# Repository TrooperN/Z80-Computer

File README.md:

# Z80-Computer

## This is a Work in Progress

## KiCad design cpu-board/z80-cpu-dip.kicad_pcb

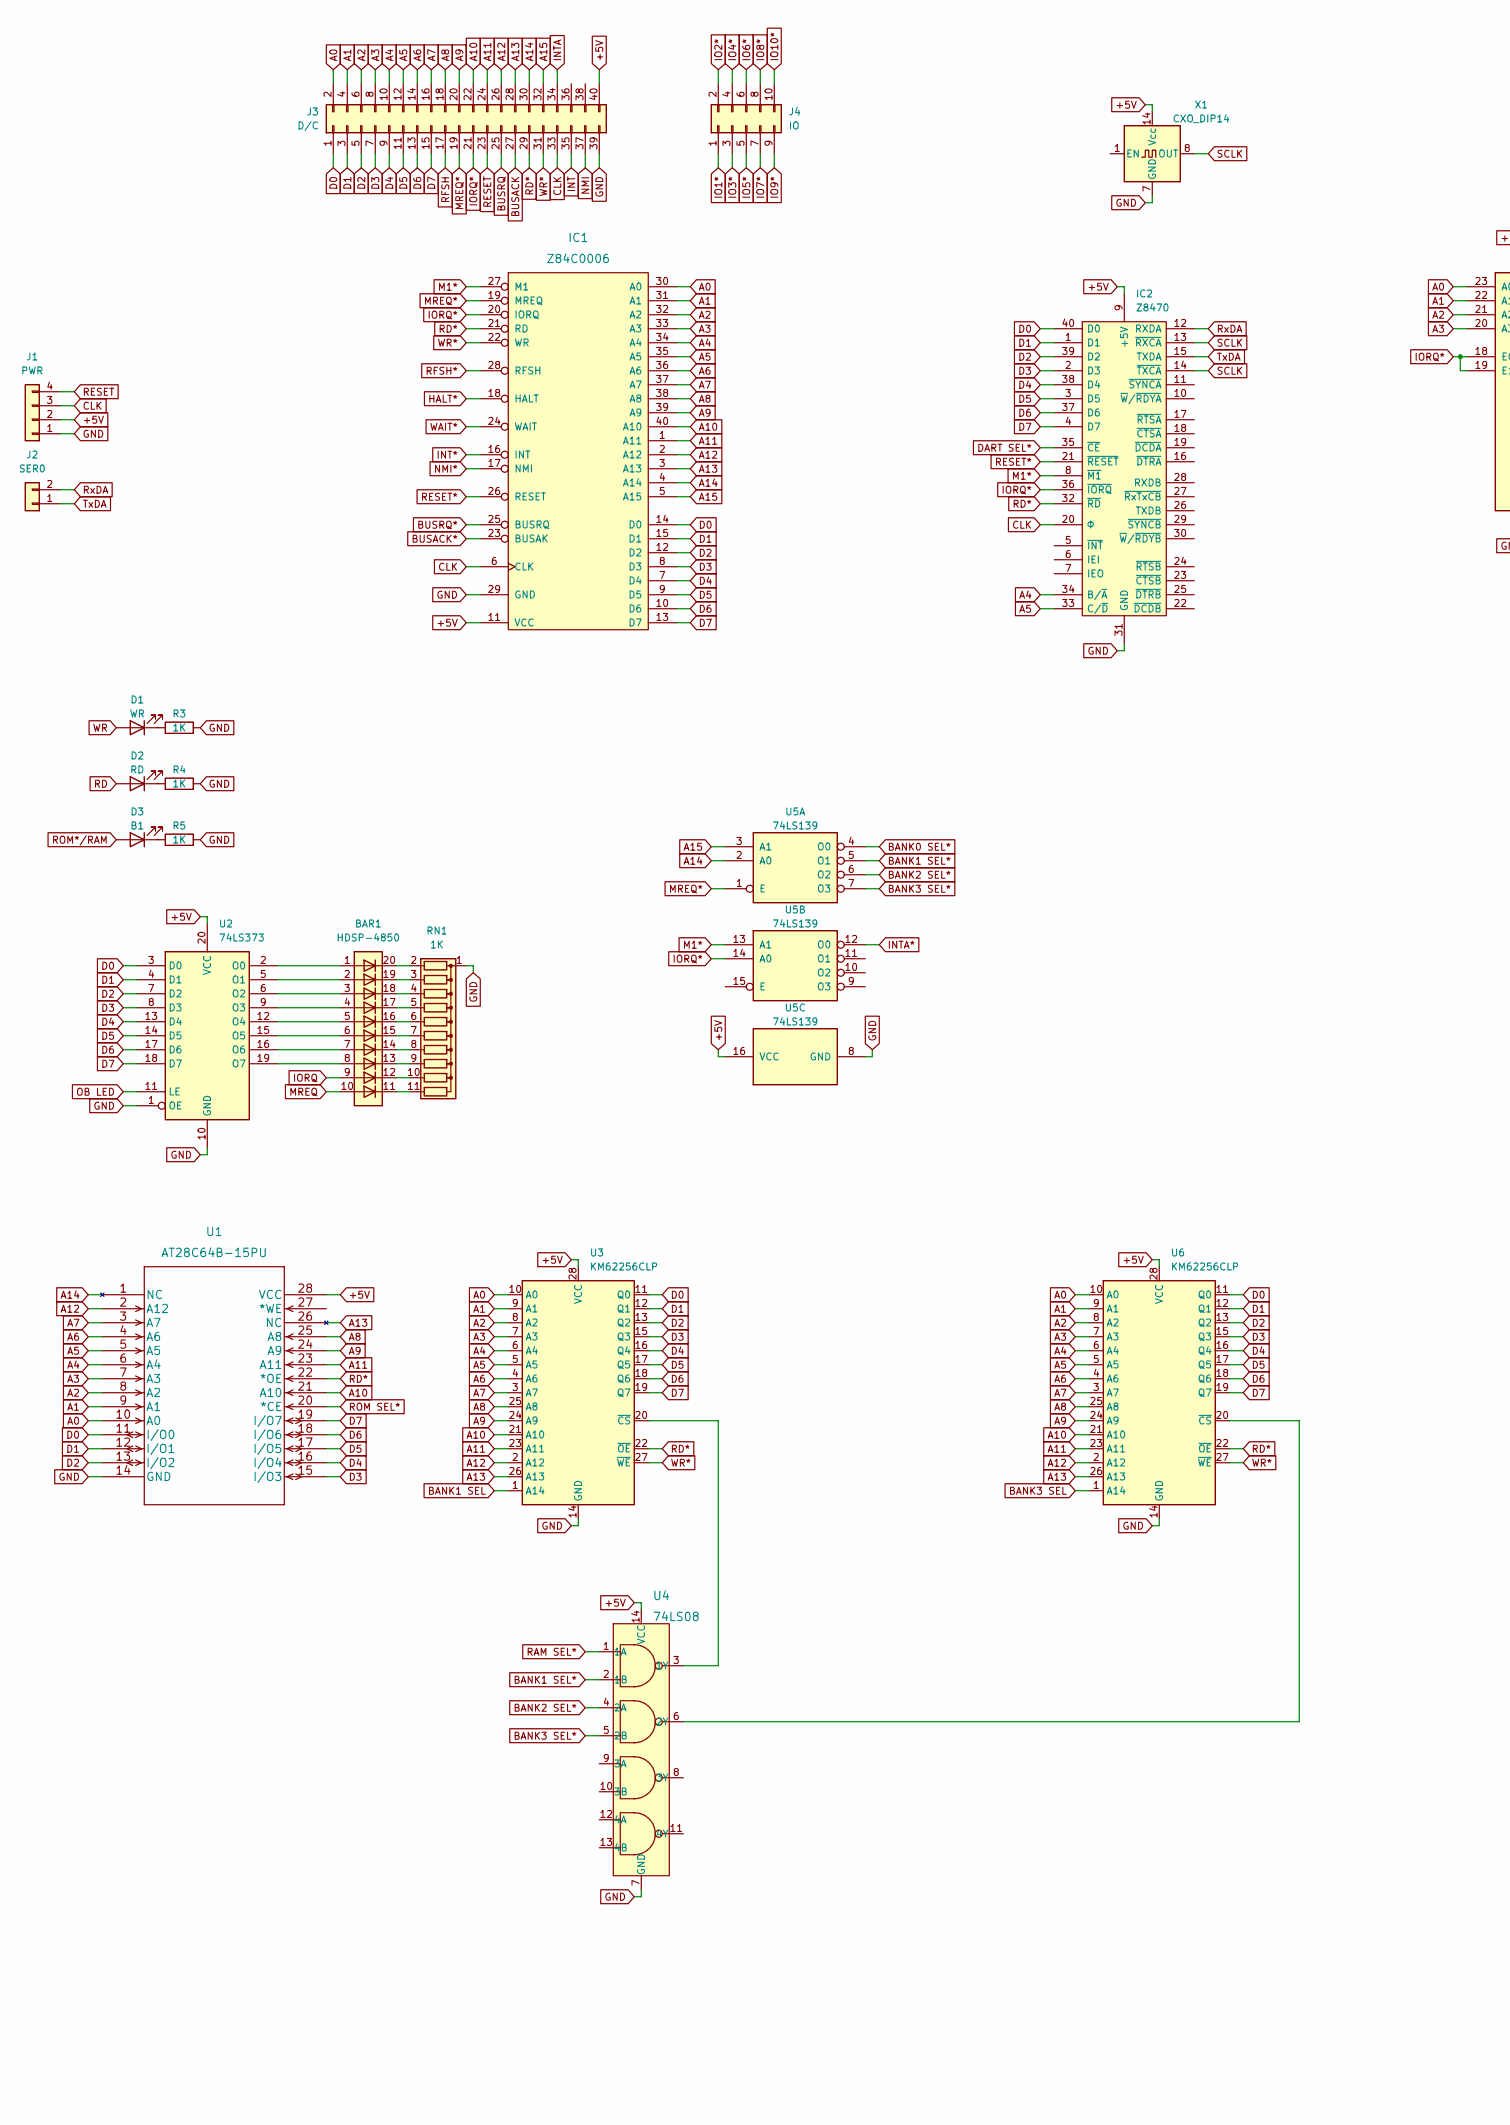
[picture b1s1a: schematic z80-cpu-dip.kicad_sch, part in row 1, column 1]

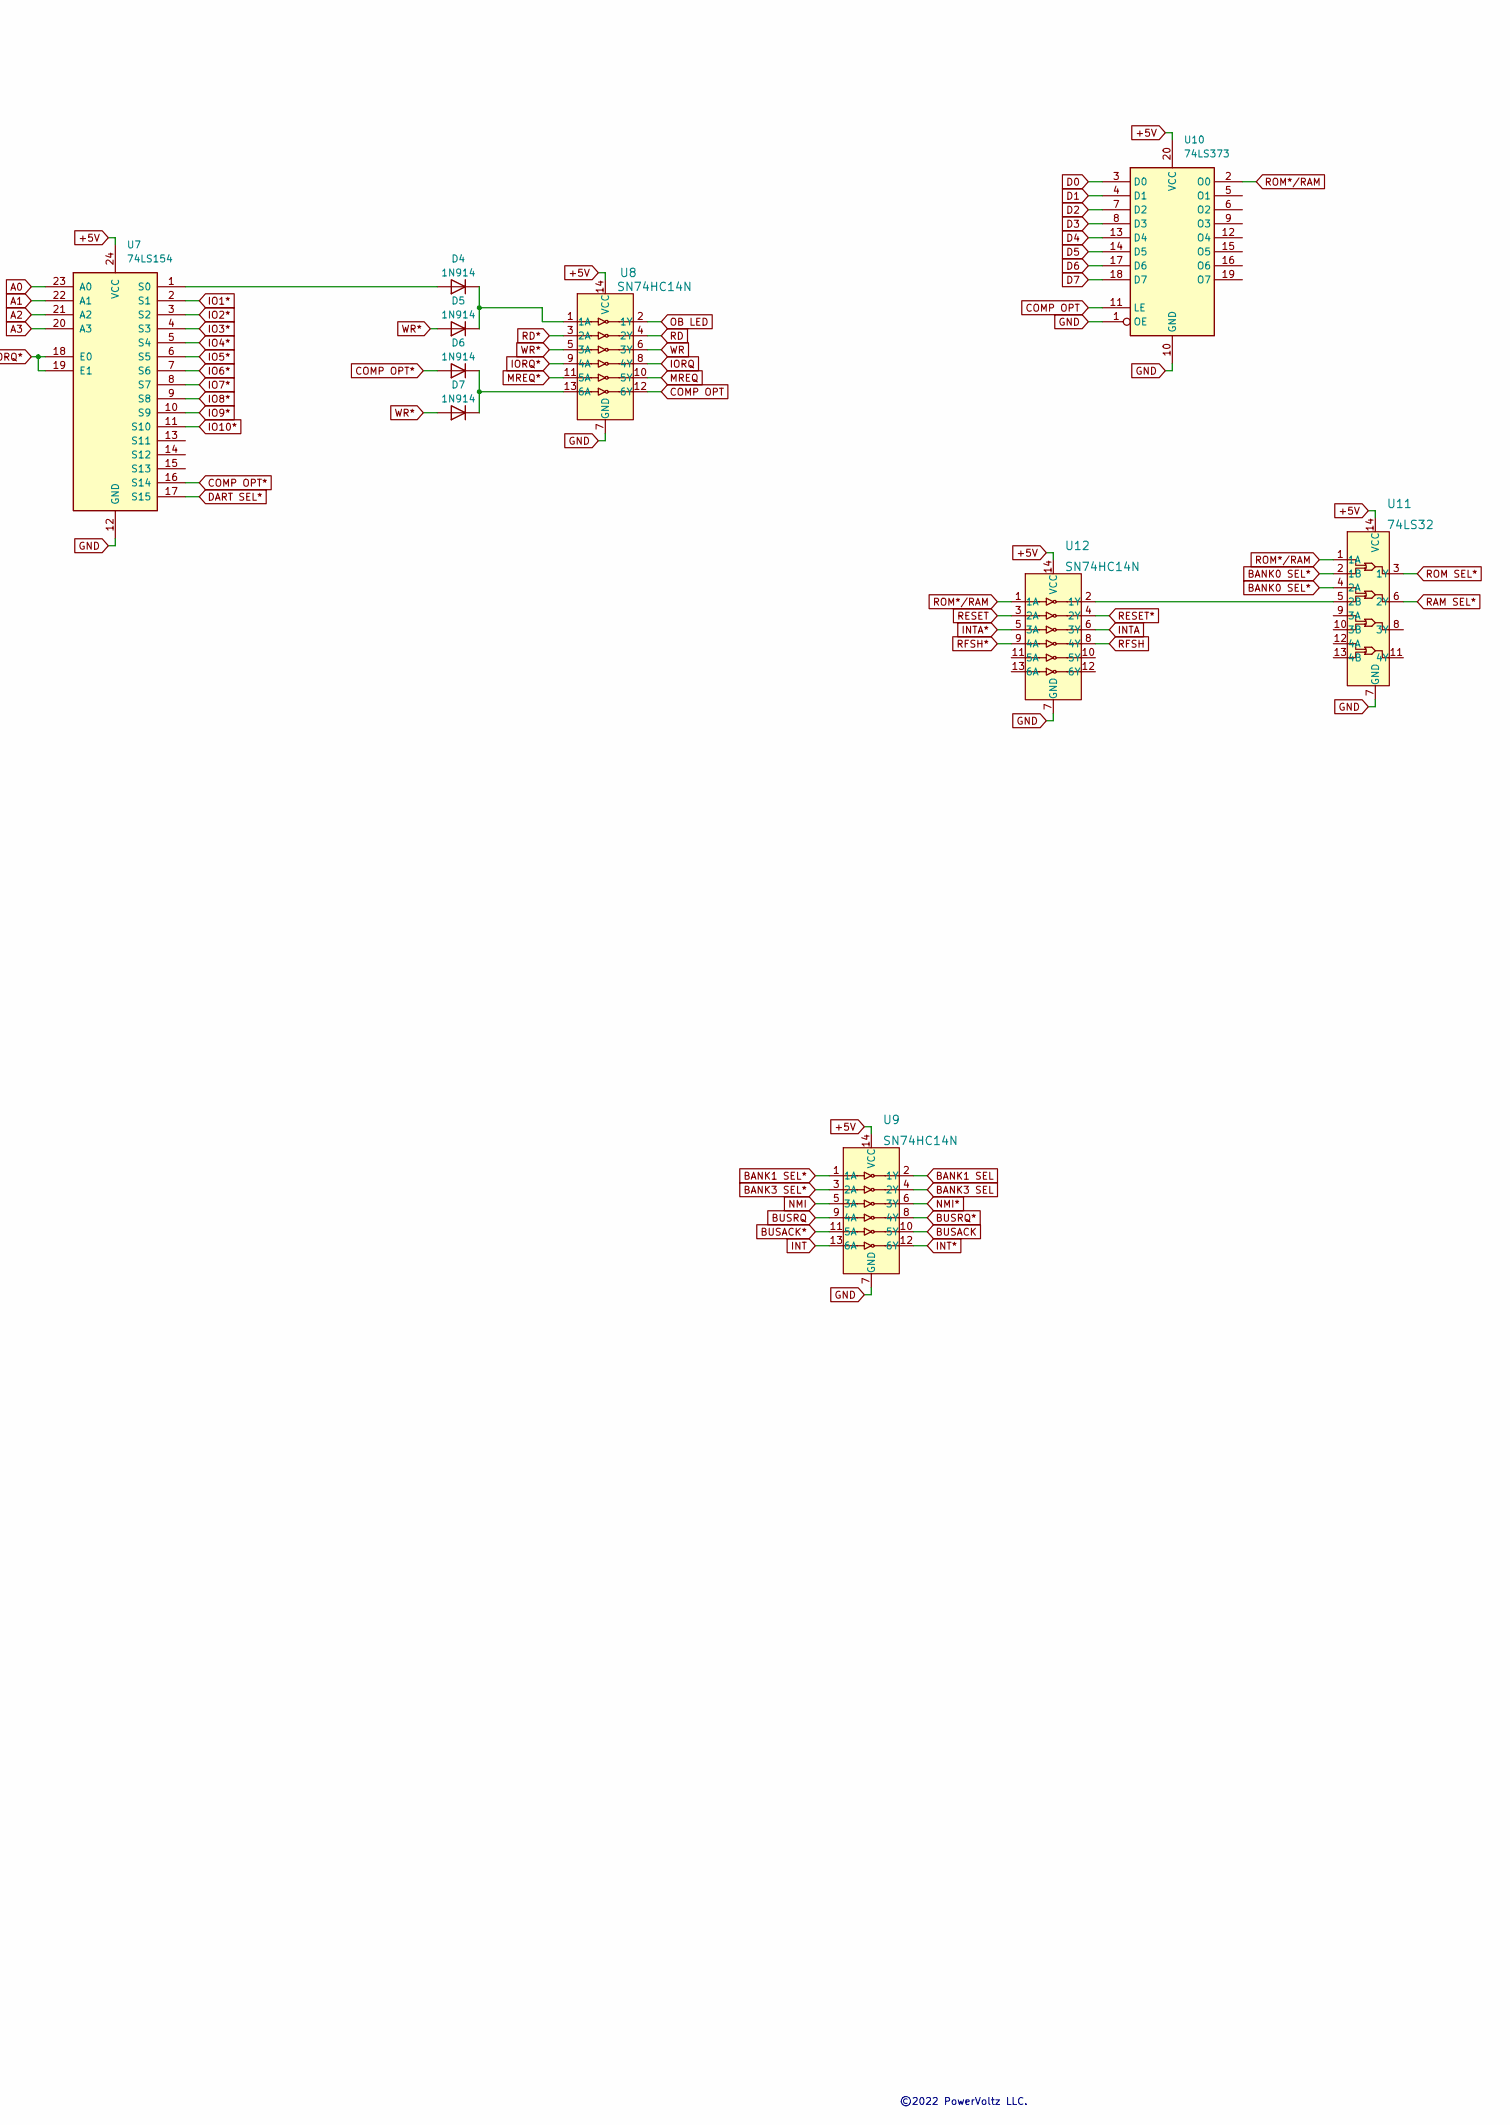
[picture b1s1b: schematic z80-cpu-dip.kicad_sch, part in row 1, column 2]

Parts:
BAR1: HDSP-4850
D1: WR; LED_D5.0mm_Horizontal_O1.27mm_Z3.0mm
D2: RD; LED_D5.0mm_Horizontal_O1.27mm_Z3.0mm
D3: B1; LED_D5.0mm_Horizontal_O1.27mm_Z3.0mm
D4, D5, D6, D7: 1N914; D_DO-35_SOD27_P7.62mm_Horizontal
IC1: Z84C0006; DIP-40_W15.24mm
IC2: Z8470; DIP-40_W15.24mm; Manufacturer_Part_Number Z84C4206PEG; Mouser Part Number 692-Z84C4206PEG
J1: PWR; PinHeader_1x04_P2.54mm_Horizontal
J2: SER0; PinHeader_1x02_P2.54mm_Horizontal
J3: D/C; PinHeader_2x20_P2.54mm_Horizontal
J4: IO; PinHeader_2x05_P2.54mm_Horizontal
R3, R4, R5: 1K; R_Axial_DIN0207_L6.3mm_D2.5mm_P10.16mm_Horizontal
RN1: 1K; R_Array_SIP11
U1: AT28C64B-15PU; DIP-28_W15.24mm_Socket
U2, U10: 74LS373; DIP-20_W7.62mm
U3, U6: KM62256CLP; DIP-28_W15.24mm
U4: 74LS08; DIP-14_W7.62mm; MPN SN74HC08N; Digi-Key_PN 296-1570-5-ND
U5: 74LS139; DIP-16_W7.62mm
U7: 74LS154; DIP-24_W15.24mm
U8, U9, U12: SN74HC14N; DIP-14_W7.62mm; MPN SN74HC14N; Digi-Key_PN 296-1577-5-ND
U11: 74LS32; DIP-14_W7.62mm; MPN SN74LS32N; Digi-Key_PN 296-1658-5-ND
X1: CXO_DIP14; Oscillator_DIP-14

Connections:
+5V: IC1.11 (VCC), IC2.9 (+5V), J1.2, J3.40, U1.28 (VCC), U2.20 (VCC), U3.28 (VCC), U4.14 (VCC), U5.16 (VCC), U6.28 (VCC), U7.24 (VCC), U8.14 (VCC), U9.14 (VCC), U10.20 (VCC), U11.14 (VCC), U12.14 (VCC), X1.14 (Vcc); also elsewhere on the board
A0: IC1.30 (A0), J3.2, U1.10 (A0), U3.10 (A0), U6.10 (A0), U7.23 (A0)
A1: IC1.31 (A1), J3.4, U1.9 (A1), U3.9 (A1), U6.9 (A1), U7.22 (A1)
A2: IC1.32 (A2), J3.6, U1.8 (A2), U3.8 (A2), U6.8 (A2), U7.21 (A2)
A3: IC1.33 (A3), J3.8, U1.7 (A3), U3.7 (A3), U6.7 (A3), U7.20 (A3)
A4: IC1.34 (A4), IC2.34 (B/~A), J3.10, U1.6 (A4), U3.6 (A4), U6.6 (A4)
A5: IC1.35 (A5), IC2.33 (C/~D), J3.12, U1.5 (A5), U3.5 (A5), U6.5 (A5)
A6: IC1.36 (A6), J3.14, U1.4 (A6), U3.4 (A6), U6.4 (A6)
A7: IC1.37 (A7), J3.16, U1.3 (A7), U3.3 (A7), U6.3 (A7)
A8: IC1.38 (A8), J3.18, U1.25 (A8), U3.25 (A8), U6.25 (A8)
A9: IC1.39 (A9), J3.20, U1.24 (A9), U3.24 (A9), U6.24 (A9)
A10: IC1.40 (A10), J3.22, U1.21 (A10), U3.21 (A10), U6.21 (A10)
A11: IC1.1 (A11), J3.24, U1.23 (A11), U3.23 (A11), U6.23 (A11)
A12: IC1.2 (A12), J3.26, U1.2 (A12), U3.2 (A12), U6.2 (A12)
A13: IC1.3 (A13), J3.28, U1.26 (NC), U3.26 (A13), U6.26 (A13)
A14: IC1.4 (A14), J3.30, U1.1 (NC), U5.2 (A0)
A15: IC1.5 (A15), J3.32, U5.3 (A1)
BANK0 SEL*: U5.4 (O0), U11.2 (1B), U11.4 (2A)
BANK1 SEL: U3.1 (A14), U9.2 (1Y)
BANK1 SEL*: U4.2 (1B), U5.5 (O1), U9.1 (1A)
BANK2 SEL*: U4.4 (2A), U5.6 (O2)
BANK3 SEL: U6.1 (A14), U9.4 (2Y)
BANK3 SEL*: U4.5 (2B), U5.7 (O3), U9.3 (2A)
BUSACK: J3.27, U9.10 (5Y)
BUSACK*: IC1.23 (BUSAK), U9.11 (5A)
BUSRQ: J3.25, U9.9 (4A)
BUSRQ*: IC1.25 (BUSRQ), U9.8 (4Y)
CLK: IC1.6 (CLK), IC2.20 (Φ), J1.3, J3.33
COMP OPT: U8.12 (6Y), U10.11 (LE)
COMP OPT*: D6.2 (A), U7.16 (S14)
D0: IC1.14 (D0), IC2.40 (D0), J3.1, U1.11 (I/O0), U2.3 (D0), U3.11 (Q0), U6.11 (Q0), U10.3 (D0)
D1: IC1.15 (D1), IC2.1 (D1), J3.3, U1.12 (I/O1), U2.4 (D1), U3.12 (Q1), U6.12 (Q1), U10.4 (D1)
D2: IC1.12 (D2), IC2.39 (D2), J3.5, U1.13 (I/O2), U2.7 (D2), U3.13 (Q2), U6.13 (Q2), U10.7 (D2)
D3: IC1.8 (D3), IC2.2 (D3), J3.7, U1.15 (I/O3), U2.8 (D3), U3.15 (Q3), U6.15 (Q3), U10.8 (D3)
D4: IC1.7 (D4), IC2.38 (D4), J3.9, U1.16 (I/O4), U2.13 (D4), U3.16 (Q4), U6.16 (Q4), U10.13 (D4)
D5: IC1.9 (D5), IC2.3 (D5), J3.11, U1.17 (I/O5), U2.14 (D5), U3.17 (Q5), U6.17 (Q5), U10.14 (D5)
D6: IC1.10 (D6), IC2.37 (D6), J3.13, U1.18 (I/O6), U2.17 (D6), U3.18 (Q6), U6.18 (Q6), U10.17 (D6)
D7: IC1.13 (D7), IC2.4 (D7), J3.15, U1.19 (I/O7), U2.18 (D7), U3.19 (Q7), U6.19 (Q7), U10.18 (D7)
DART SEL*: IC2.35 (~CE), U7.17 (S15)
GND: IC1.29 (GND), IC2.31 (GND), J1.1, J3.39, R3.2, R4.2, R5.2, RN1.1 (common), U1.14 (GND), U2.1 (OE), U2.10 (GND), U3.14 (GND), U4.7 (GND), U5.8 (GND), U6.14 (GND), U7.12 (GND), U8.7 (GND), U9.7 (GND), U10.1 (OE), U10.10 (GND), U11.7 (GND), U12.7 (GND), X1.7 (GND); also elsewhere on the board
HALT*: IC1.18 (HALT)
INT: J3.35, U9.13 (6A)
INT*: IC1.16 (INT), U9.12 (6Y)
INTA: J3.34, U12.6 (3Y)
INTA*: U5.12 (O0), U12.5 (3A)
IO1*: J4.1, U7.2 (S1)
IO2*: J4.2, U7.3 (S2)
IO3*: J4.3, U7.4 (S3)
IO4*: J4.4, U7.5 (S4)
IO5*: J4.5, U7.6 (S5)
IO6*: J4.6, U7.7 (S6)
IO7*: J4.7, U7.8 (S7)
IO8*: J4.8, U7.9 (S8)
IO9*: J4.9, U7.10 (S9)
IO10*: J4.10, U7.11 (S10)
IORQ: BAR1.9 (A), U8.8 (4Y)
IORQ*: IC1.20 (IORQ), IC2.36 (~IORQ), J3.21, U5.14 (A0), U7.18 (E0), U7.19 (E1), U8.9 (4A)
M1*: IC1.27 (M1), IC2.8 (~M1), U5.13 (A1)
MREQ: BAR1.10 (A), U8.10 (5Y)
MREQ*: IC1.19 (MREQ), J3.19, U5.1 (E), U8.11 (5A)
NMI: J3.37, U9.5 (3A)
NMI*: IC1.17 (NMI), U9.6 (3Y)
unnamed: BAR1.1 (A), U2.2 (O0)
unnamed: BAR1.2 (A), U2.5 (O1)
unnamed: BAR1.3 (A), U2.6 (O2)
unnamed: BAR1.4 (A), U2.9 (O3)
unnamed: BAR1.5 (A), U2.12 (O4)
unnamed: BAR1.6 (A), U2.15 (O5)
unnamed: BAR1.7 (A), U2.16 (O6)
unnamed: BAR1.8 (A), U2.19 (O7)
unnamed: BAR1.11 (K), RN1.11 (R10)
unnamed: BAR1.12 (K), RN1.10 (R9)
unnamed: BAR1.13 (K), RN1.9 (R8)
unnamed: BAR1.14 (K), RN1.8 (R7)
unnamed: BAR1.15 (K), RN1.7 (R6)
unnamed: BAR1.16 (K), RN1.6 (R5)
unnamed: BAR1.17 (K), RN1.5 (R4)
unnamed: BAR1.18 (K), RN1.4 (R3)
unnamed: BAR1.19 (K), RN1.3 (R2)
unnamed: BAR1.20 (K), RN1.2 (R1)
unnamed: D1.1 (K), R3.1
unnamed: D2.1 (K), R4.1
unnamed: D3.1 (K), R5.1
unnamed: D4.1 (K), D5.1 (K), U8.1 (1A)
unnamed: D4.2 (A), U7.1 (S0)
unnamed: D6.1 (K), D7.1 (K), U8.13 (6A)
unnamed: U3.20 (~CS), U4.3 (1Y)
unnamed: U4.6 (2Y), U6.20 (~CS)
unnamed: U11.5 (2B), U12.2 (1Y)
OB LED: U2.11 (LE), U8.2 (1Y)
RAM SEL*: U4.1 (1A), U11.6 (2Y)
RD: D2.2 (A), U8.4 (2Y)
RD*: IC1.21 (RD), IC2.32 (~RD), J3.29, U1.22 (*OE), U3.22 (~OE), U6.22 (~OE), U8.3 (2A)
RESET: J1.4, J3.23, U12.3 (2A); also elsewhere on the board
RESET*: IC1.26 (RESET), IC2.21 (~RESET), U12.4 (2Y); also elsewhere on the board
RFSH: J3.17, U12.8 (4Y)
RFSH*: IC1.28 (RFSH), U12.9 (4A)
ROM SEL*: U1.20 (*CE), U11.3 (1Y)
ROM*/RAM: D3.2 (A), U10.2 (O0), U11.1 (1A), U12.1 (1A)
RxDA: IC2.12 (RXDA), J2.2
SCLK: IC2.13 (~RXCA), IC2.14 (~TXCA), X1.8 (OUT)
TxDA: IC2.15 (TXDA), J2.1
WAIT*: IC1.24 (WAIT)
WR: D1.2 (A), U8.6 (3Y)
WR*: D5.2 (A), D7.2 (A), IC1.22 (WR), J3.31, U3.27 (~WE), U6.27 (~WE), U8.5 (3A)

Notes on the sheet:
©2022 PowerVoltz LLC.

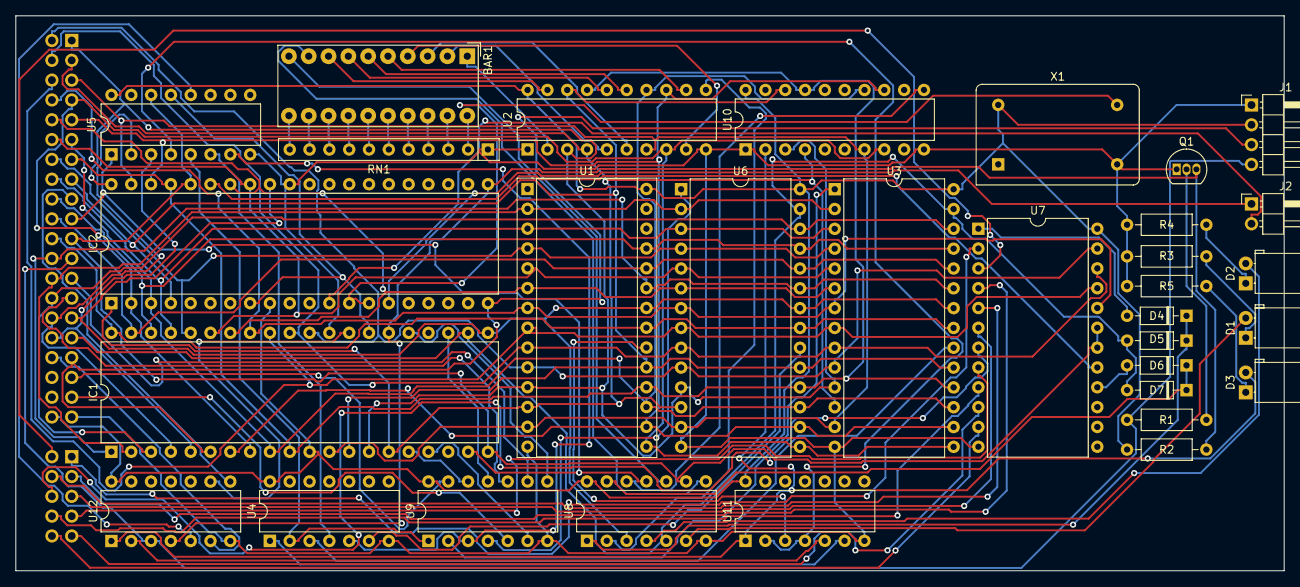
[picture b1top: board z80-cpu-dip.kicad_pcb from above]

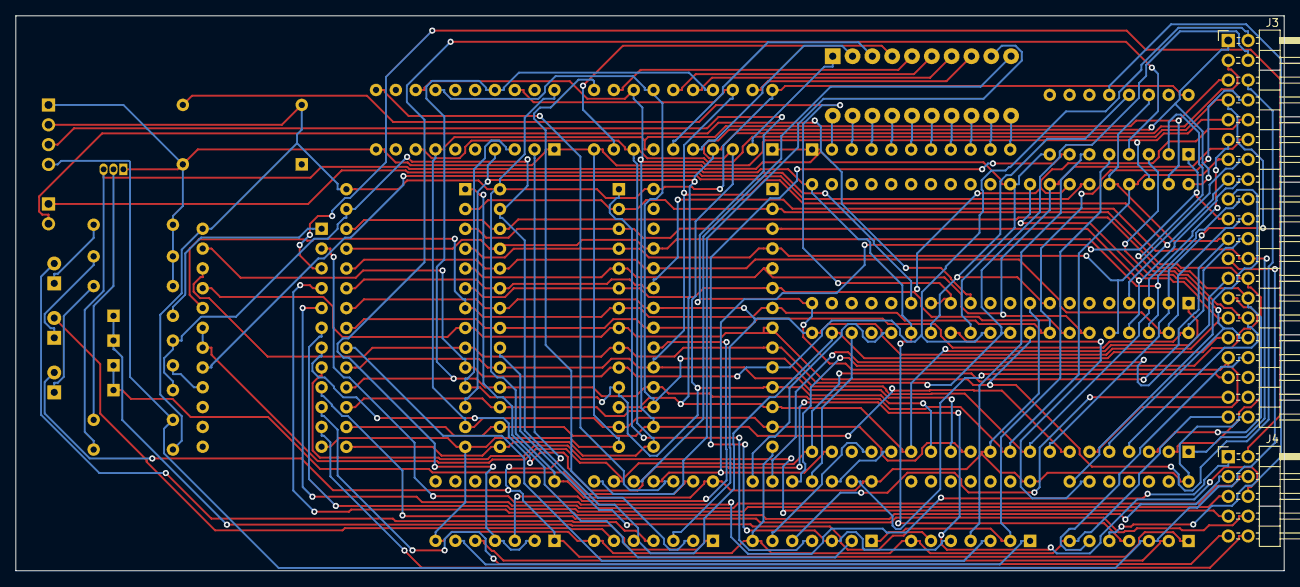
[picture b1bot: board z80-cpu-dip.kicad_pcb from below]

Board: 2 copper layers, 162.6 x 71.1 mm, 34 parts (2 on the bottom side), 104 nets.

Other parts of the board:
Q1: 2N3904; TO-92_Inline
R1, R2: 1K; R_Axial_DIN0207_L6.3mm_D2.5mm_P10.16mm_Horizontal

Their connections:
+5V: R2.1; also elsewhere on the board
GND: Q1.1 (E); also elsewhere on the board
unnamed: Q1.2 (B), R1.2
RESET: R1.1; also elsewhere on the board
RESET*: Q1.3 (C), R2.2; also elsewhere on the board

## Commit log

2022-01-11 Added Z80 MCU DIP.kicad_sch
2022-01-11 Added Required Digikey Symbol Libraries
2022-01-11 Added PCB, renamed SCH
2022-01-11 Renamed Stuff
2022-01-29 Updated PCB and SCH
2022-01-29 Added Cpu Boardview
